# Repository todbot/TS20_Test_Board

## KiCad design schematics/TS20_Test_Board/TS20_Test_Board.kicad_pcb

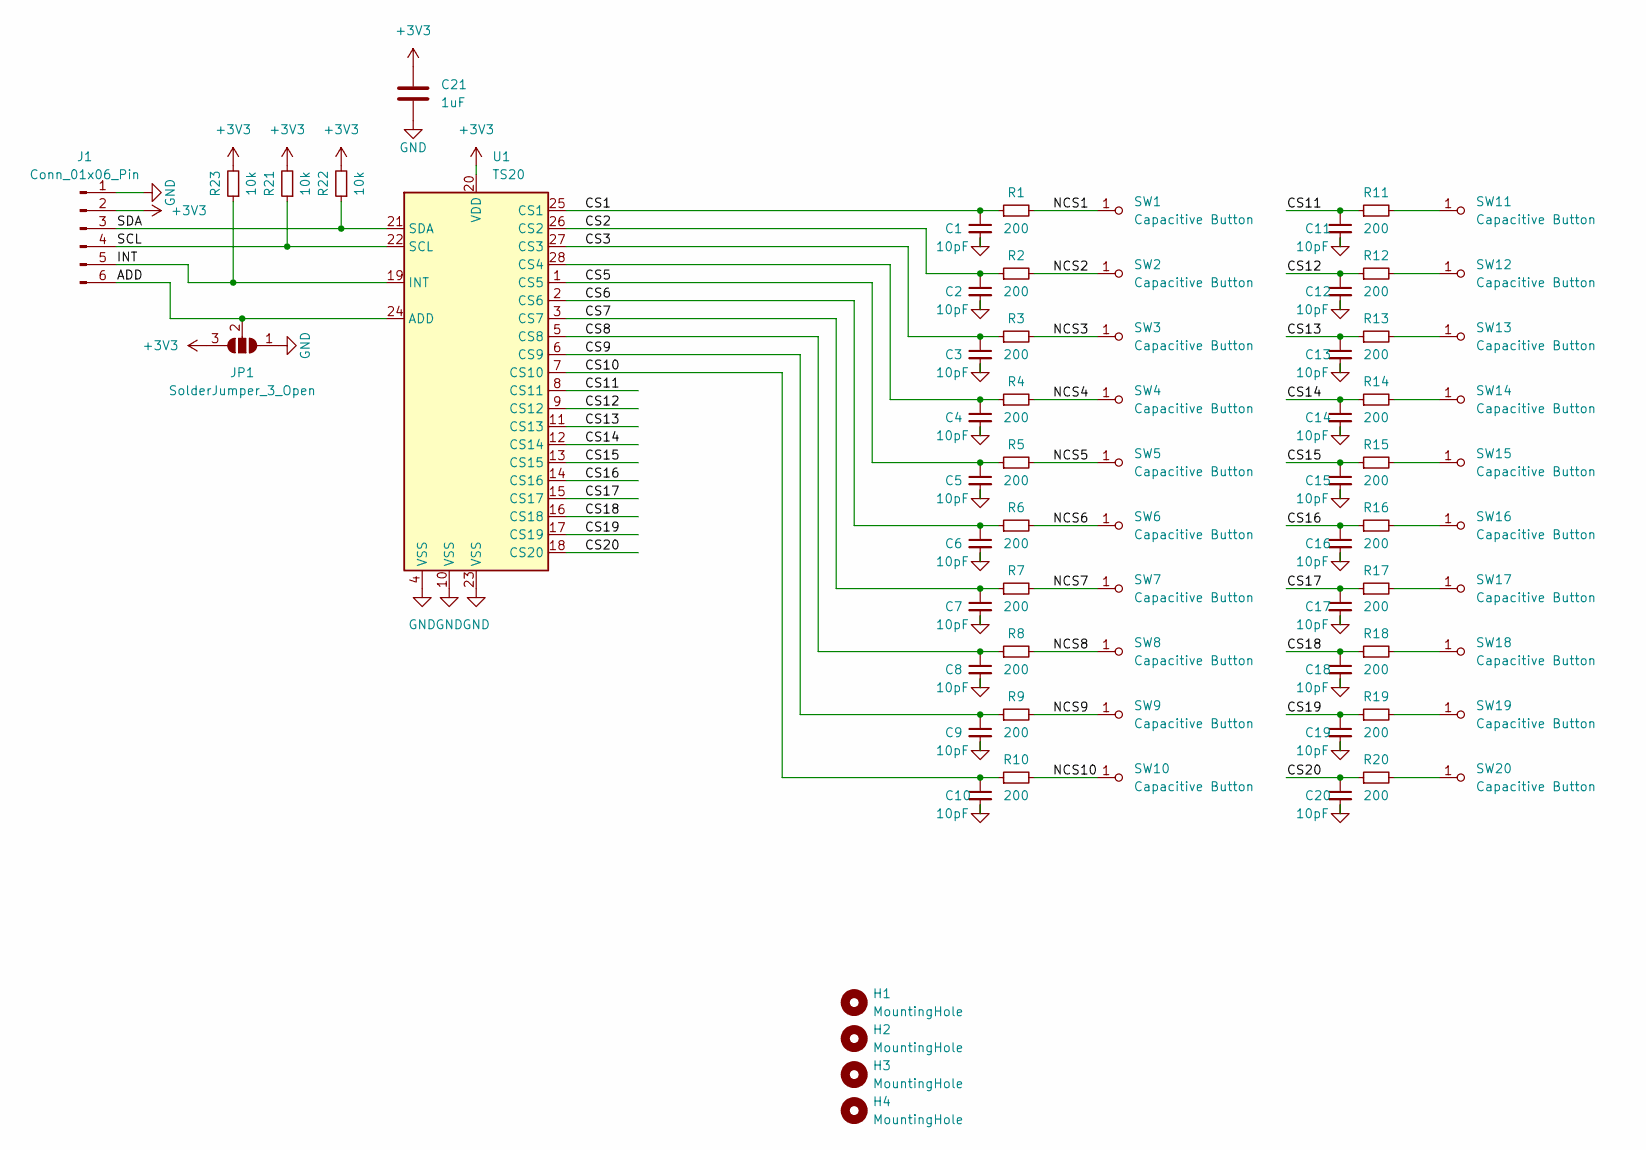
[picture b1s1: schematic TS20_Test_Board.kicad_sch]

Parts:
C1, C2, C3, C4, C5, C6, C7, C8, C9, C10, C11, C12, C13, C14, C15, C16, C17, C18, C19, C20: 10pF; C_0603_1608Metric
C21: 1uF; C_0603_1608Metric
H1, H2, H3, H4: MountingHole; MountingHole_2.5mm
J1: Conn_01x06_Pin; PinHeader_1x06_P2.54mm_Vertical
JP1: SolderJumper_3_Open; SolderJumper-3_P1.3mm_Open_RoundedPad1.0x1.5mm
R1, R2, R3, R4, R5, R6, R7, R8, R9, R10, R11, R12, R13, R14, R15, R16, R17, R18, R19, R20: 200; R_0603_1608Metric
R21, R22, R23: 10k; R_0603_1608Metric
SW1, SW2, SW3, SW4, SW5, SW6, SW7, SW8, SW9, SW10, SW11, SW12, SW13, SW14, SW15, SW16, SW17, SW18, SW19, SW20: Capacitive Button; Pad-CapacitiveTouch
U1: TS20; TSSOP-28_4.4x9.7mm_P0.65mm

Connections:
+3V3: C21.1, J1.2, JP1.3 (B), R21.2, R22.2, R23.2, U1.20 (VDD)
/ADD: J1.6, JP1.2 (C), U1.24 (ADD)
/CS1: C1.1, R1.1, U1.25 (CS1)
/CS2: C2.1, R2.1, U1.26 (CS2)
/CS3: C3.1, R3.1, U1.27 (CS3)
/CS5: C5.1, R5.1, U1.1 (CS5)
/CS6: C6.1, R6.1, U1.2 (CS6)
/CS7: C7.1, R7.1, U1.3 (CS7)
/CS8: C8.1, R8.1, U1.5 (CS8)
/CS9: C9.1, R9.1, U1.6 (CS9)
/CS10: C10.1, R10.1, U1.7 (CS10)
/CS11: C11.1, R11.1, U1.8 (CS11)
/CS12: C12.1, R12.1, U1.9 (CS12)
/CS13: C13.1, R13.1, U1.11 (CS13)
/CS14: C14.1, R14.1, U1.12 (CS14)
/CS15: C15.1, R15.1, U1.13 (CS15)
/CS16: C16.1, R16.1, U1.14 (CS16)
/CS17: C17.1, R17.1, U1.15 (CS17)
/CS18: C18.1, R18.1, U1.16 (CS18)
/CS19: C19.1, R19.1, U1.17 (CS19)
/CS20: C20.1, R20.1, U1.18 (CS20)
/INT: J1.5, R23.1, U1.19 (INT)
/NCS1: R1.2, SW1.1 (A)
/NCS2: R2.2, SW2.1 (A)
/NCS3: R3.2, SW3.1 (A)
/NCS4: R4.2, SW4.1 (A)
/NCS5: R5.2, SW5.1 (A)
/NCS6: R6.2, SW6.1 (A)
/NCS7: R7.2, SW7.1 (A)
/NCS8: R8.2, SW8.1 (A)
/NCS9: R9.2, SW9.1 (A)
/NCS10: R10.2, SW10.1 (A)
/SCL: J1.4, R21.1, U1.22 (SCL)
/SDA: J1.3, R22.1, U1.21 (SDA)
GND: C1.2, C2.2, C3.2, C4.2, C5.2, C6.2, C7.2, C8.2, C9.2, C10.2, C11.2, C12.2, C13.2, C14.2, C15.2, C16.2, C17.2, C18.2, C19.2, C20.2, C21.2, J1.1, JP1.1 (A), U1.4 (VSS), U1.10 (VSS), U1.23 (VSS)
unnamed: R11.2, SW11.1 (A)
unnamed: R12.2, SW12.1 (A)
unnamed: R13.2, SW13.1 (A)
unnamed: R14.2, SW14.1 (A)
unnamed: R15.2, SW15.1 (A)
unnamed: R16.2, SW16.1 (A)
unnamed: R17.2, SW17.1 (A)
unnamed: R18.2, SW18.1 (A)
unnamed: R19.2, SW19.1 (A)
unnamed: R20.2, SW20.1 (A)
unnamed: C4.1, R4.1, U1.28 (CS4)

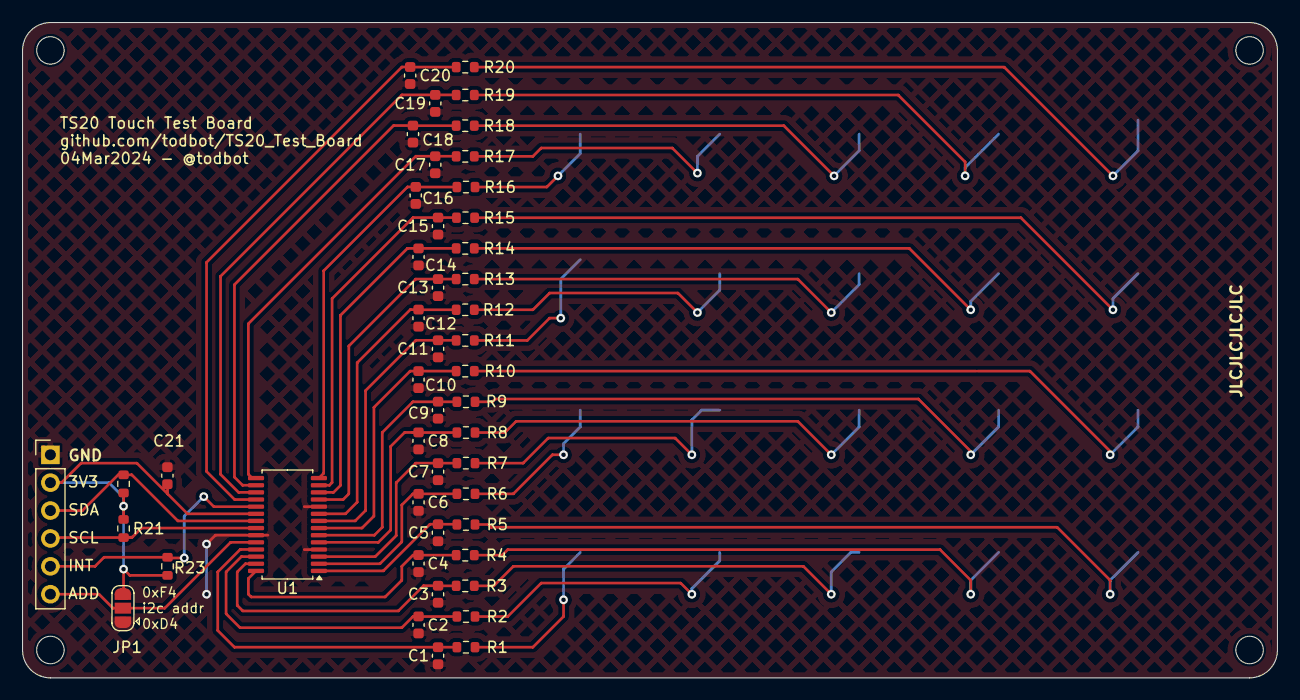
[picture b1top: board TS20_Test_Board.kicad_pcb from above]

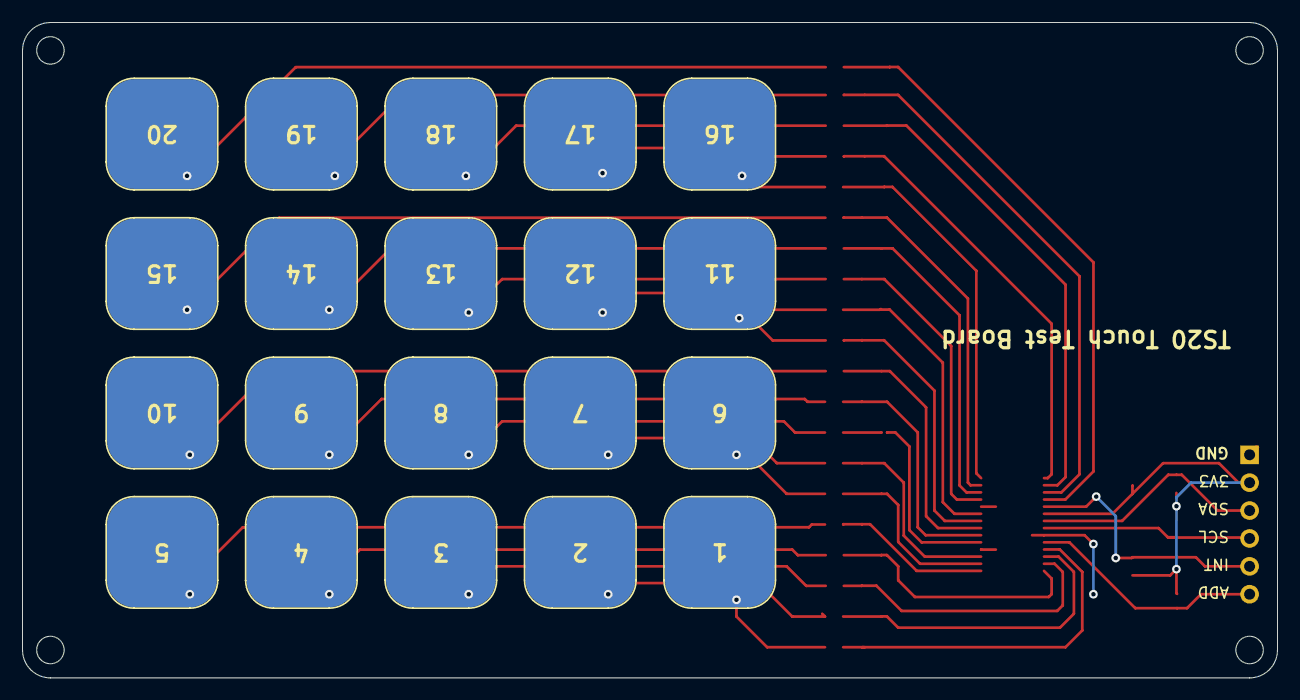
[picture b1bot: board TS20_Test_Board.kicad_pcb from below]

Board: 2 copper layers, 114.3 x 59.7 mm, 71 parts (20 on the bottom side), 46 nets.

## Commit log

2024-03-07 first
2024-03-07 add JLC marking
2024-03-07 cleanup
2024-03-07 update gitignore for extra kicad dribble
2024-03-12 basic arduino library
2024-03-12 first cut at circuitpython lib
2024-03-13 circuitpython two board test
